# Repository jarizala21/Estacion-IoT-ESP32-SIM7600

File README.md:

# Estación IoT de Monitorización de Temperatura

Proyecto de estación autónoma basada en **ESP32 + SIM7600** que mide temperatura y envía los datos a **Google Sheets mediante LTE**.

El sistema está diseñado para funcionar durante largos periodos con **baterías 18650** utilizando **deep sleep**.

---

# Hardware

Elementos principales utilizados:

- ESP32
- Módulo LTE **SIM7600**
- Sensor **PT100** con **MAX31865**
- Sensor **LM35** (temperatura interna)
- Baterías **18650**
- Circuito de carga **MCP73871**
- Load switch **TPS22918**
- PCB diseñada en **KiCad**

---

# Funcionamiento

El sistema funciona de la siguiente manera:

1. El ESP32 se despierta desde **deep sleep**
2. Enciende el **SIM7600**
3. Se conecta a la red LTE
4. Sincroniza la hora mediante **NTP**
5. Lee los sensores
6. Envía los datos a **Google Sheets**
7. Apaga el módem
8. Vuelve a **deep sleep**

Actualmente el sistema envía datos a:

- **08:45**
- **13:00**

---

# Firmware

El firmware está desarrollado en **C++ usando PlatformIO**.

Características:

- Comunicación LTE mediante comandos AT
- Sincronización de hora con NTP
- Lectura de sensores
- Envío HTTP a Google Sheets
- Gestión de batería
- Deep sleep

El código se encuentra en:

Firmware/EstacionIot/src/main.cpp

---

# Esquema eléctrico

El esquema del sistema se puede consultar aquí:

[Esquema del sistema](Hardware/Proyecto/Esquema_V1.pdf)

---

# PCB

La PCB fue diseñada con **KiCad**.

Los archivos del proyecto se encuentran en:

Hardware/Proyecto

---

# Autor

Proyecto desarrollado por:

**Jonathan Arizala**

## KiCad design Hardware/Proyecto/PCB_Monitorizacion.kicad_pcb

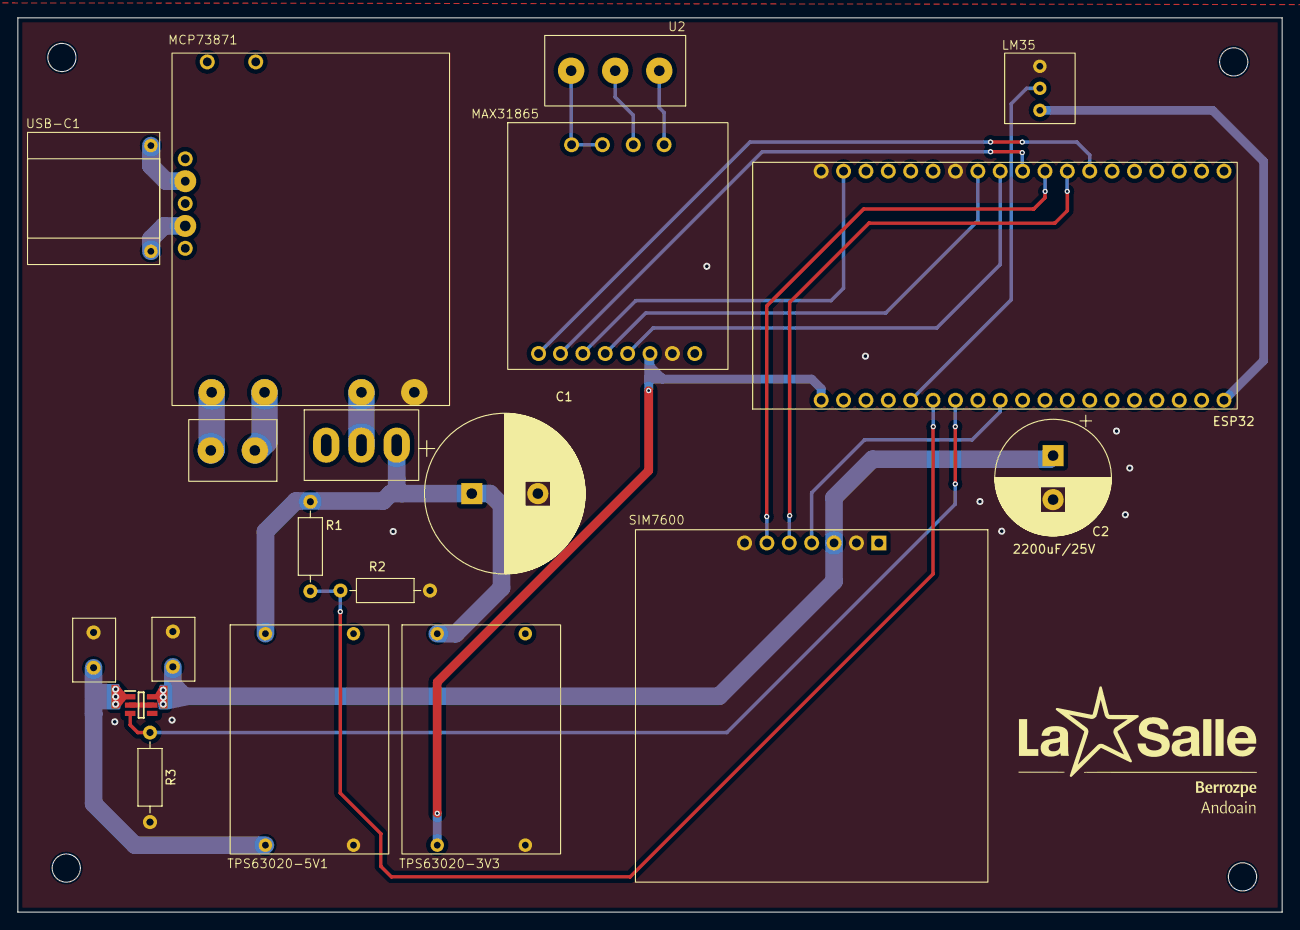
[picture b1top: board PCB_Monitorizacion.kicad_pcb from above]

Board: 2 copper layers, 143.5 x 101.5 mm, 19 parts (0 on the bottom side), 26 nets.

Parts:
C1: 4700uF/35V; CP_Radial_D18.0mm_P7.50mm
C2: 2200uF/25V; CP_Radial_D13.0mm_P5.00mm
C3, C4: 1uF/63V; Cap_7.5mm_5mm
ESP32: ESP32
IC1: TPS22918TDBVTQ1; SOT95P280X145-6N
Inter1: Interruptor3Pines
LM35: LM35
MAX31865: MAX31865
MCP73871: MCP73871
R1: 22k; R_Axial_DIN0207_L6.3mm_D2.5mm_P10.16mm_Horizontal
R2: 10k; R_Axial_DIN0207_L6.3mm_D2.5mm_P10.16mm_Horizontal
R3: 100k; R_Axial_DIN0207_L6.3mm_D2.5mm_P10.16mm_Horizontal
SIM7600: SIM7600
TPS63020-3V3, TPS63020-5V1: TPS63020
U1: Conn5mm_02x01
U2: Conn5mm_03x01
USB-C1: USB-C

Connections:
3V3: ESP32.2 (3V3), MAX31865.6 (3V3), TPS63020-3V3.3 (OUT)
5V: C3.2, IC1.1 (VIN), TPS63020-5V1.3 (OUT)
DIV_TENS: ESP32.18 (GPIO35), R1.1, R2.2
GND: C1.2, C2.2, C3.1, C4.1, ESP32.1 (GND), ESP32.9 (GND), IC1.2 (GND), IC1.5 (QOD), LM35.2 (-), MAX31865.5 (GND), MCP73871.4 (GND), R2.1, R3.2, SIM7600.1 (GND), SIM7600.6 (GND), TPS63020-3V3.4 (GND), TPS63020-5V1.4 (GND)
unnamed: ESP32.8 (5V), LM35.1 (+)
unnamed: ESP32.7 (GPIO4), MAX31865.11 (RDY)
unnamed: ESP32.6 (GPIO5), MAX31865.10 (CS)
unnamed: ESP32.15 (GPIO16), SIM7600.3 (T)
unnamed: ESP32.16 (GPIO17), SIM7600.2 (R)
unnamed: ESP32.3 (GPIO18), MAX31865.7 (CLK)
unnamed: ESP32.4 (GPIO19), MAX31865.8 (SDD)
unnamed: ESP32.5 (GPIO23), MAX31865.9 (SDI)
unnamed: ESP32.14 (GPIO25), SIM7600.4 (X)
unnamed: ESP32.10 (GPIO34), LM35.3 (SEÑAL)
unnamed: MAX31865.3 (RTD+), MAX31865.4 (F+), U2.3 (RED)
unnamed: MAX31865.1 (F-), U2.1 (BK)
unnamed: MAX31865.2 (RTD-), U2.2 (BK)
unnamed: MCP73871.6 (+), USB-C1.1 (+)
unnamed: MCP73871.5 (-), USB-C1.2 (-)
unnamed: MCP73871.1 (BATT+), U1.1 (BATT+)
unnamed: MCP73871.2 (BATT-), U1.2 (BATT-)
unnamed: TPS63020-3V3.2 (GND), TPS63020-5V1.2 (GND)
unnamed: Inter1.1, MCP73871.3 (LOAD)
unnamed: C1.1, Inter1.3, R1.2, TPS63020-3V3.1 (VIN), TPS63020-5V1.1 (VIN)
ON: ESP32.11 (GPIO32), IC1.3 (ON), R3.1
VOUT: C2.1, C4.2, IC1.6 (VOUT), SIM7600.5 (5V)

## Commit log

2026-03-10 Primer commit del firmware estación IoT
    Añadido proyecto PlatformIO con estructura inicial y configuración.
2026-03-10 Primer commit del firmware estación IoT
2026-03-10 Primer commit del Hardware
